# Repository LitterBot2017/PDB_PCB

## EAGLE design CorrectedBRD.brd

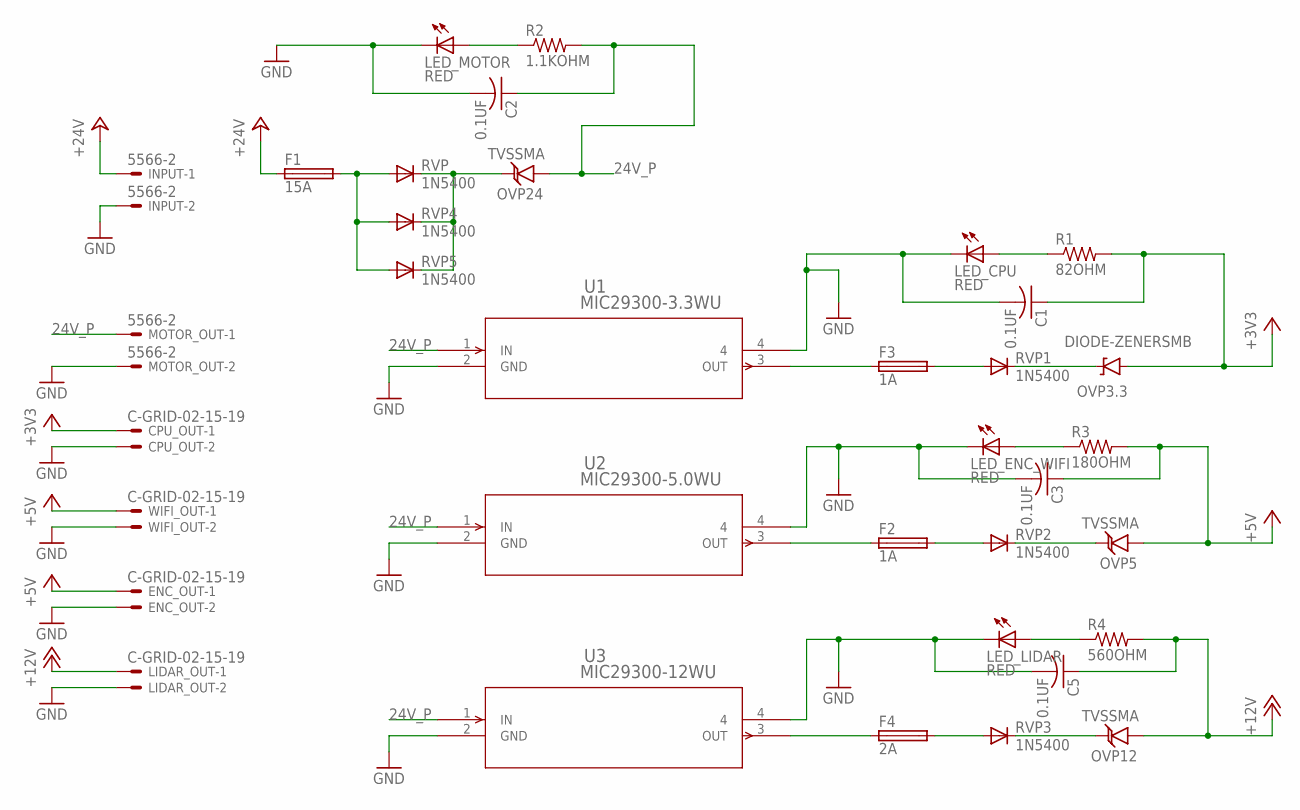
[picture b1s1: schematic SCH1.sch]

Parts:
C1, C2, C3, C5: 0.1UF; C1206
CPU_OUT: C-GRID-02-15-19; 15-91-02
ENC_OUT: C-GRID-02-15-19; 15-91-02
F1: 15A; TE5
F2, F3: 1A; TE5
F4: 2A; TE5
INPUT: 5566-2
LED_CPU: RED; 1206
LED_ENC_WIFI: RED; 1206
LED_LIDAR: RED; 1206
LED_MOTOR: RED; 1206
LIDAR_OUT: C-GRID-02-15-19; 15-91-02
MOTOR_OUT: 5566-2
OVP3.3: DIODE-ZENERSMB; SMB-DIODE
OVP5, OVP12, OVP24: TVSSMA; SMA-DIODE
R1: 82OHM; R1206W
R2: 1.1KOHM; R1206W
R3: 180OHM; R1206W
R4: 560OHM; R1206W
RVP, RVP1, RVP2, RVP3, RVP4, RVP5: 1N5400; DO201-15
U1: MIC29300-3.3WU; TO-263-3
U2: MIC29300-5.0WU; TO-263-3
U3: MIC29300-12WU; TO-263-3
WIFI_OUT: C-GRID-02-15-19; 15-91-02

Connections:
24V_P: C2.1, MOTOR_OUT.1, OVP24.A, R2.2, U1.1 (IN), U2.1 (IN), U3.1 (IN)
+3V3: C1.1, CPU_OUT.1, OVP3.3.A, R1.2
+5V: C3.1, ENC_OUT.1, OVP5.A, R3.2, WIFI_OUT.1
+12V: C5.1, LIDAR_OUT.1, OVP12.A, R4.2
+24V: F1.1, INPUT.1
GND: C1.2, C2.2, C3.2, C5.2, CPU_OUT.2, ENC_OUT.2, INPUT.2, LED_CPU.C, LED_ENC_WIFI.C, LED_LIDAR.C, LED_MOTOR.C, LIDAR_OUT.2, MOTOR_OUT.2, U1.2 (GND), U1.4, U2.2 (GND), U2.4, U3.2 (GND), U3.4, WIFI_OUT.2
unnamed: F1.2, RVP.A, RVP4.A, RVP5.A
unnamed: OVP24.C, RVP.C, RVP4.C, RVP5.C
unnamed: F3.1, U1.3 (OUT)
unnamed: F2.1, U2.3 (OUT)
unnamed: F4.1, U3.3 (OUT)
unnamed: F3.2, RVP1.A
unnamed: F2.2, RVP2.A
unnamed: F4.2, RVP3.A
unnamed: OVP3.3.C, RVP1.C
unnamed: OVP5.C, RVP2.C
unnamed: OVP12.C, RVP3.C
unnamed: LED_CPU.A, R1.1
unnamed: LED_MOTOR.A, R2.1
unnamed: LED_ENC_WIFI.A, R3.1
unnamed: LED_LIDAR.A, R4.1

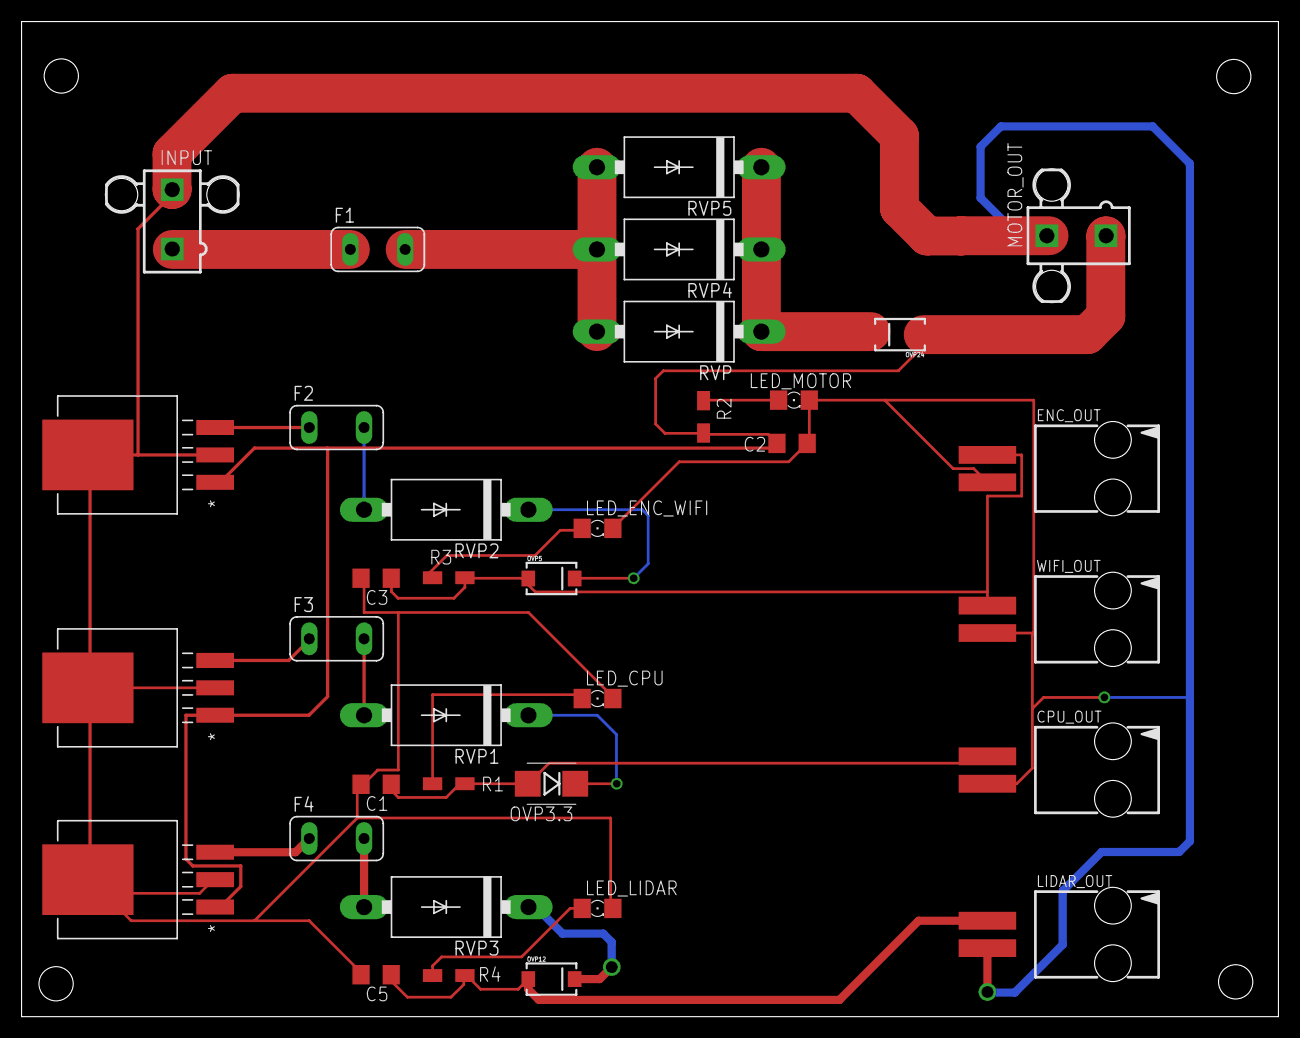
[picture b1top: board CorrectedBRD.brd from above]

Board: 2 copper layers, 116.5 x 92.2 mm, 35 parts (0 on the bottom side), 21 nets.

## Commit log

2016-10-02 initial commit schematic done
2016-10-02 broad completed
2016-10-04 adding drawnig files
2016-10-07 Changed some of the trace widths new file CorrectedBRD
2016-10-07 made changes to the CAD stuff

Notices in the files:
parts and their libraries:
SparkFun-DiscreteSemi: Licensing: Creative Commons ShareAlike 4.0 International - https://creativecommons.org/licenses/by-sa/4.0
COPYRIGHT: Copyright (C) 2015 Accelerated Designs. All rights reserved
